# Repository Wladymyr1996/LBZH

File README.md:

# LBZH
Repoitory for KiCAD project LBZH (Simple Laboratory Power Supply).

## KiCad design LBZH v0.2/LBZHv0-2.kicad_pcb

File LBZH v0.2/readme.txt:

У цій альфа-версії працює стбалізація за напругою та струмом.
Криво працює вивід сигналу поточної напруги. Коли йде стабілізація за струмом,напруга на виході игналу може піднятися на 0.5В.

! Зверніть увагу, що вихід землі не не з'єднаний з входом землі на плату.

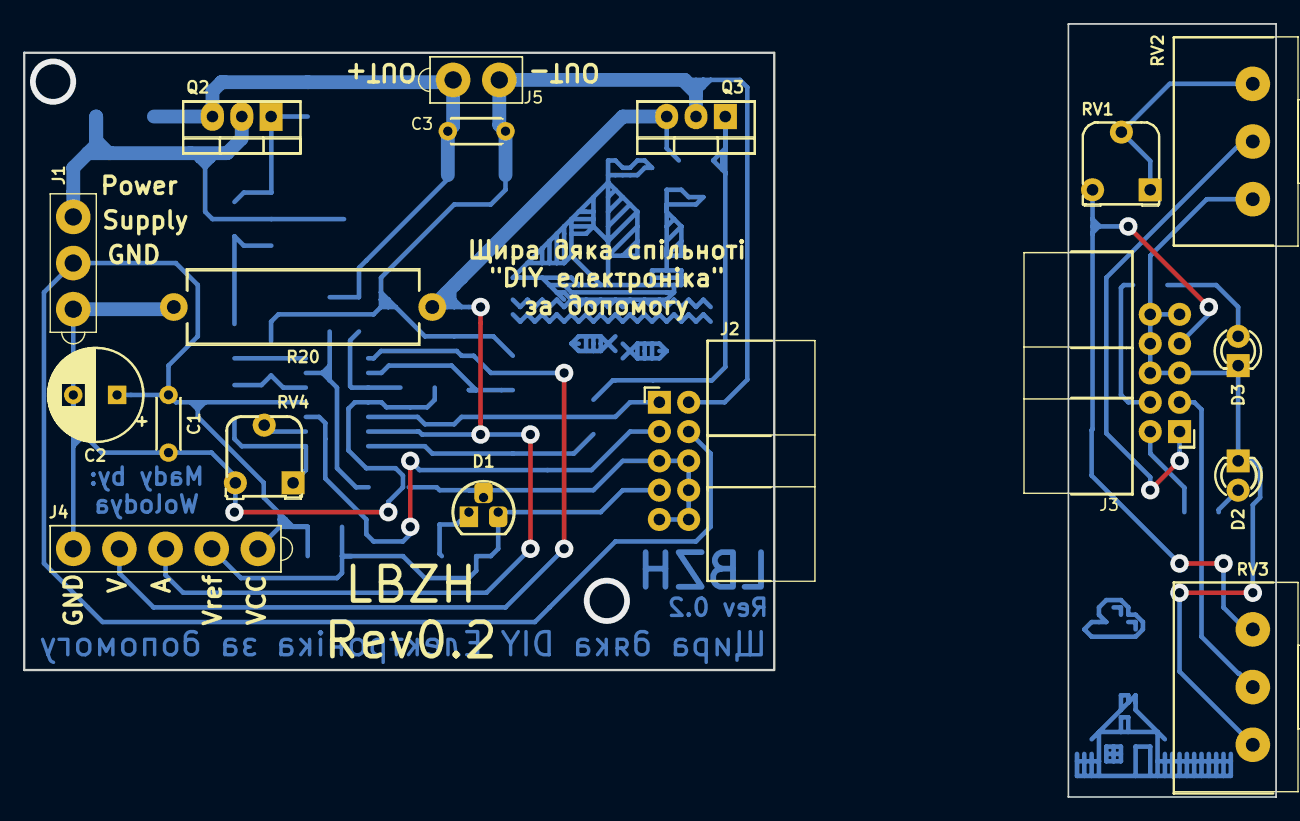
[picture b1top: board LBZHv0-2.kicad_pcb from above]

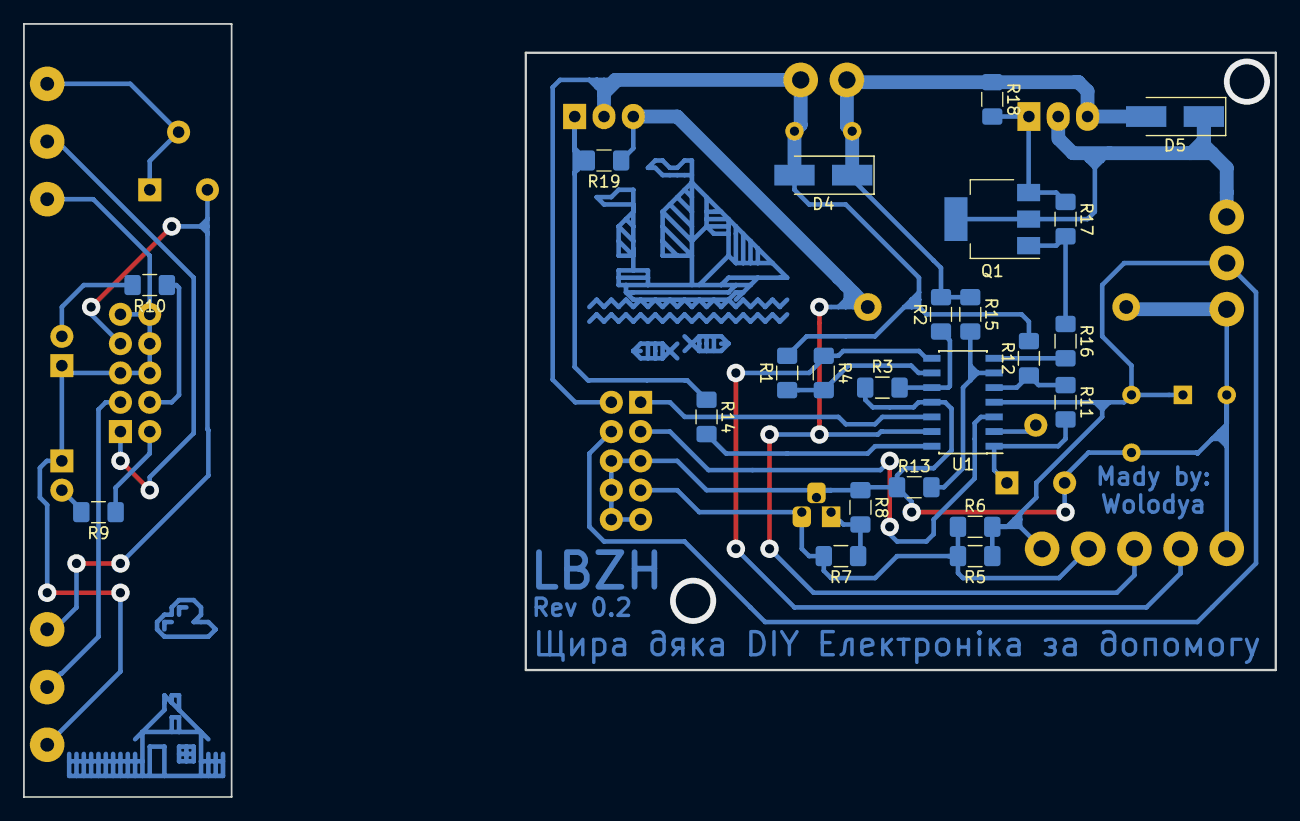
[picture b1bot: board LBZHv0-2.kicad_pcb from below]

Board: 2 copper layers, 108.5 x 67.0 mm, 41 parts (23 on the bottom side), 31 nets.

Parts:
C1, C3: 100nF; C_Disc_D4.3mm_W1.9mm_P5.00mm
C2: 100uF; CP_Radial_D8.0mm_P3.80mm
D1: TL431LP; TO-92_HandSolder
D2: Load; LED_D3.0mm_FlatTop
D3: Power; LED_D3.0mm_FlatTop
D4, D5: SMA4007; D_SMA_Handsoldering
J1: PowerIn; Conn_1x3_d1.5mm
J2: BusOut; IDC-Header_2x05_P2.54mm_Horizontal
J3: BusIn; IDC-Header_2x05_P2.54mm_Horizontal
J4: VAmetr; Conn_1x5_d1.5mm
J5: OUT; Conn_1x2_d1.5mm
Q1: BCP56; SOT-223
Q2: 2SC3039; TO-220-3_Vertical
Q3: IRF640; TO-220-3_Vertical
R1, R2, R3, R4, R7, R11, R12, R13, R15: 4.7K; R_1206_3216Metric_Pad1.42x1.75mm_HandSolder
R5, R6, R9, R10: 2.2K; R_1206_3216Metric_Pad1.42x1.75mm_HandSolder
R8: 5.1K; R_1206_3216Metric_Pad1.42x1.75mm_HandSolder
R14, R16: 100; R_1206_3216Metric_Pad1.42x1.75mm_HandSolder
R17, R18, R19: 100K; R_1206_3216Metric_Pad1.42x1.75mm_HandSolder
R20: 0.51; R_Axial_Power_L20.0mm_W6.4mm_P22.40mm
RV1, RV4: 20K; Potentiometer_Runtron_RM-065_Vertical
RV2, RV3: 2.2K; Potentiometer_Alps_RK163_Single_Horizontal
U1: LM324; SOIC-14_3.9x8.7mm_P1.27mm

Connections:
GNDA: C1.2, C2.2, D1.2, J1.1, J2.5, J2.6, J2.8, J2.9, J2.10, J4.5, R3.1, R8.1, R13.1, R20.2, RV4.3, U1.11
GND_p: D2.1, D3.1, J3.5, J3.6, J3.8, J3.9, J3.10, RV2.1, RV3.1
Iadj: J2.1, U1.12
Iadj_p: J3.1, RV2.2
LoadSig_p: J3.2, R9.1
unnamed: D1.1, R7.1, R8.2
unnamed: D2.2, R9.2
unnamed: D3.2, R10.2
unnamed: Q1.1, R16.1, R17.2
unnamed: Q1.3, Q2.1, R17.1, R18.2
unnamed: Q3.1, R14.1, R19.2
unnamed: R1.1, R4.2, U1.9
unnamed: R2.1, R3.2, U1.10
unnamed: R11.1, R12.1, U1.5
unnamed: R11.2, RV4.1, U1.1
unnamed: R13.2, R15.2, U1.6
unnamed: R14.2, U1.14
unnamed: R16.2, U1.7
unnamed: RV1.1, RV1.2, RV2.3
unnamed: RV4.2, U1.2
OUT+: C3.1, D4.1, D5.2, J5.1, Q2.3, R2.2, R15.1, R18.1
OUT-: C3.2, D4.2, J2.2, J5.2, Q3.2, R1.2, R12.2
VCC: D5.1, J1.3, Q1.2, Q1.4, Q2.2
VDD: C1.1, C2.1, J1.2, J2.4, J4.1, R5.1, R6.2, U1.4
VDD_p: J3.4, R10.1
Vadj: J2.3, U1.3
Vadj_p: J3.3, RV3.2
Vref: D1.3, J2.7, J4.2, R5.2, R6.1, R7.2
Vref_p: J3.7, RV1.3, RV3.3
Vshunt: J4.3, Q3.3, R19.1, R20.1, U1.13
Vvalue: J4.4, R4.1, U1.8
